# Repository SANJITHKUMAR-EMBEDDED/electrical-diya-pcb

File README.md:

Electrical Diya PCB (Tutorial Project)

This is a beginner-level KiCad PCB project for an electrical diya using:
- LDR (light sensor)
- Microphone
- LED
- 3.3V Coin Cell

🔧 What I Learned
- Using KiCad for schematic and layout
- Assigning footprints and generating Gerber files
- Understanding PCB layers and board design

⚠️ This project is based on a tutorial and not tested in hardware.

 📁 Structure
- `pcb/` – KiCad PCB layout
- `gerber/` – Gerber + drill files for fabrication
- `images/` – Screenshots of schematic/PCB/3D view

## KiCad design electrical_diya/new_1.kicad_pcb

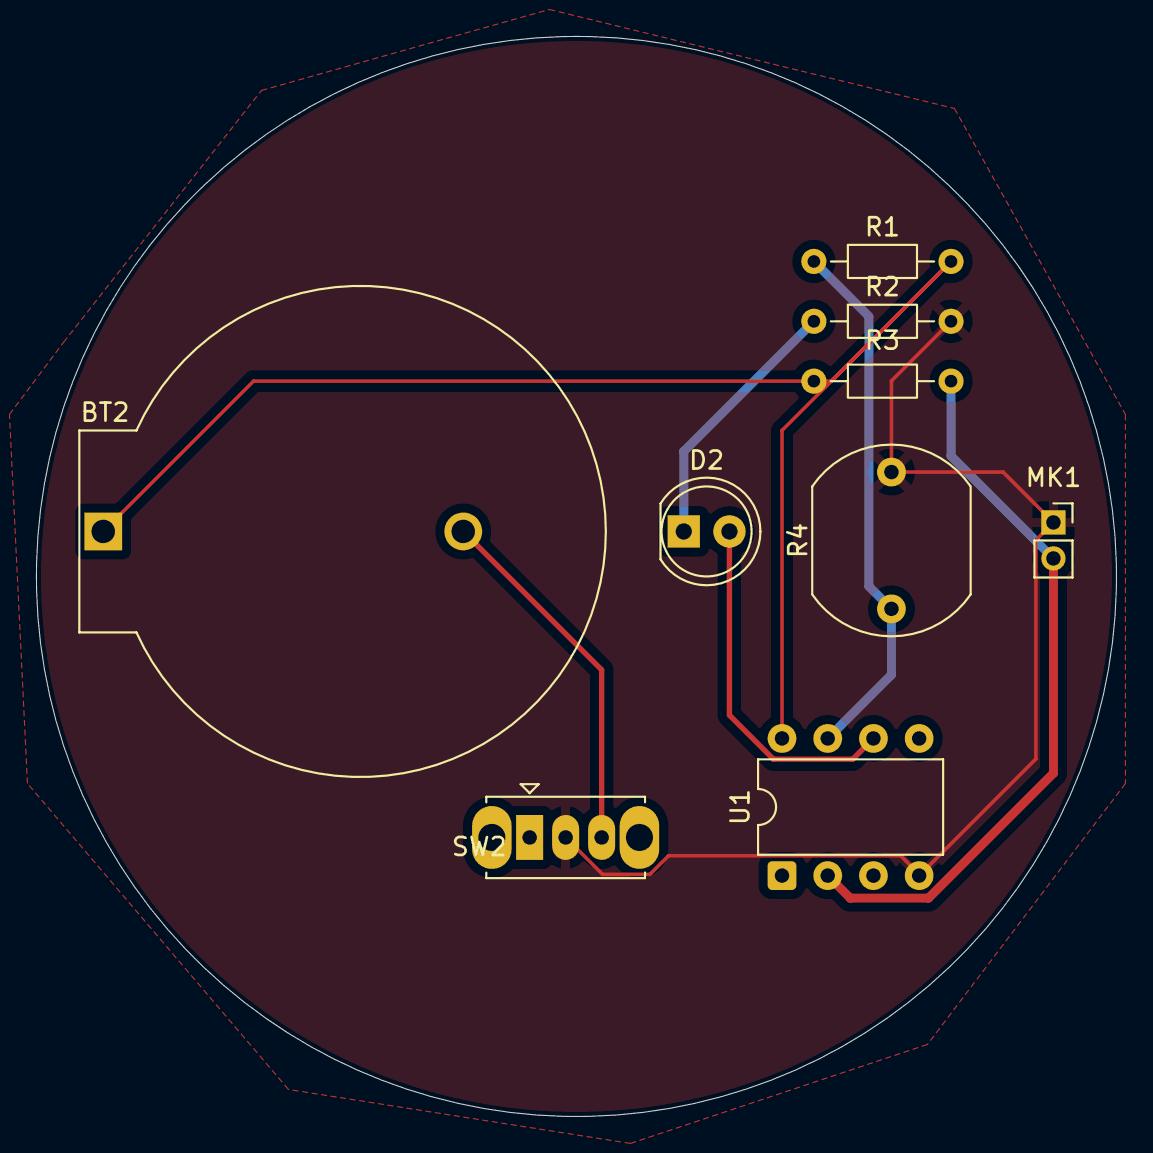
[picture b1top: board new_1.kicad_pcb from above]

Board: 2 copper layers, 60.0 x 60.0 mm, 9 parts (0 on the bottom side), 7 nets.

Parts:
BT2: 3.3v cell; BatteryHolder_ComfortableElectronic_CH273-2450_1x2450
D2: 5mm YELLOW LED; LED_D5.0mm
MK1: Microphone_Condenser; PinSocket_1x02_P2.00mm_Vertical
R1: 10K; R_Axial_DIN0204_L3.6mm_D1.6mm_P7.62mm_Horizontal
R2: 470R; R_Axial_DIN0204_L3.6mm_D1.6mm_P7.62mm_Horizontal
R3: 5.6K; R_Axial_DIN0204_L3.6mm_D1.6mm_P7.62mm_Horizontal
R4: 5mm LDR; R_LDR_10x8.5mm_P7.6mm_Vertical
SW2: SW_SPDT; SW_Slide_SPDT_Straight_CK_OS102011MS2Q
U1: ATtiny85V-10P; DIP-8_W7.62mm

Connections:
+3.3V: BT2.1 (+), R1.2, R3.1, U1.8 (VCC)
/<NO NET>: D2.2 (A), U1.6 (PB1)
/LDR: R1.1, R4.1, U1.7 (PB2)
/MIC: MK1.2 (+), R3.2, U1.2 (XTAL1/PB3)
GND: MK1.1 (-), R2.2, R4.2, SW2.2 (B), U1.4 (GND)
unnamed: BT2.2 (-), SW2.3 (C)
unnamed: D2.1 (K), R2.1

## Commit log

2025-08-29 Initial commit: Electrical Diya PCB project
2025-08-29 Rename readme.md.txt to README.md
2025-08-29 Add SVG to pcb_images folder
